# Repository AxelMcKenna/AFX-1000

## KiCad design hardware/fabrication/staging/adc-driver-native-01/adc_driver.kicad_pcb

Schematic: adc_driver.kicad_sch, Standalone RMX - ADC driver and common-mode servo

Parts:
C1, C2, C15, C16: 1pF C0G +/-0.1pF; C_0402_1005Metric
C3, C17: 47pF C0G 5%; C_0805_2012Metric
C4, C5, C18, C19: 22pF C0G 5%; C_0805_2012Metric
C6, C20: 100nF 25V X7R; C_0805_2012Metric
C7, C21: 1uF 63V film 10%; C_Rect_L7.2mm_W5.0mm_P5.00mm
C8, C22: 10uF 16V X7R; C_1206_3216Metric
C9, C23: 47uF 25V X7S; C_1210_3225Metric
C10, C11, C24, C25: 47uF 6.3V X7S; C_1206_3216Metric
C12, C26: 2.2uF 16V X7R; C_0805_2012Metric
C13, C14, C27, C28: 100nF 16V X7R; C_0402_1005Metric
C29, C30, C31, C32: 100nF 50V X7R; C_0805_2012Metric
C33, C34: 10uF 50V X7R; C_1206_3216Metric
C35, C36: 100nF 16V X7R; C_0603_1608Metric
D1, D2: BAT54S,215; SOT-23
J1: Conn_01x03; PinHeader_1x03_P2.54mm_Vertical
J2: Conn_02x10_Odd_Even; PinHeader_2x10_P2.54mm_Vertical
J3, J4: Conn_01x04; PinHeader_1x04_P2.54mm_Vertical
R1, R2, R17, R18: 2.49k 0.05%; R_0402_1005Metric
R3, R4, R19, R20: 1.21k 0.05%; R_0402_1005Metric
R5, R6, R21, R22: 3.3R 1%; R_0805_2012Metric
R7, R23: 1M 1%; R_0805_2012Metric
R8, R9, R24, R25: 100k 0.01%; R_0805_2012Metric
R10, R11, R26, R27: 10k 0.1%; R_0805_2012Metric
R12, R28: 10M 1%; R_0805_2012Metric
R13, R29: 10k 1%; R_0805_2012Metric
R14, R30: 47k 1%; R_0805_2012Metric
R15, R31: 68k 1%; R_0805_2012Metric
R16, R32: 0.1R 1%; R_0805_2012Metric
R33: 1k 1%; R_0805_2012Metric
R34, R36: 100k 0.01%; R_0603_1608Metric
R35, R37, R39, R41: 10k 0.01%; R_0603_1608Metric
R38: 161k 0.01%; R_0805_2012Metric
R40: 240k 0.01%; R_0805_2012Metric
R42, R43: 10k 1%; R_0603_1608Metric
R44: 100k 1%; R_0603_1608Metric
U1, U2: THS4551IDGKR; VSSOP-8_3x3mm_P0.65mm
U3: OPA1656ID; SOIC-8_3.9x4.9mm_P1.27mm
U4: OPA4192ID; SOIC-14_3.9x8.7mm_P1.27mm
U5, U6: LM7705MM/NOPB; VSSOP-8_3x3mm_P0.65mm
U7: TLV9024DR; SOIC-14_3.9x8.7mm_P1.27mm
U8: TPS3808G50DBVR; SOT-23-6

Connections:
/ADC_LN: C3.2, C5.1, J2.4, R6.2
/ADC_LP: C3.1, C4.1, J2.1, R5.2
/ADC_RN: C17.2, C19.1, J2.12, R22.2
/ADC_RP: C17.1, C18.1, J2.9, R21.2
/AGND: C4.2, C5.2, C6.2, C9.2, C10.2, C11.2, C12.2, C13.2, C14.2, C18.2, C19.2, C20.2, C23.2, C24.2, C25.2, C26.2, C27.2, C28.2, C29.2, C30.2, C31.2, C32.2, C33.2, C34.2, C35.2, C36.2, D1.1 (A1), D2.1 (A1), J1.2, J2.3, J2.6, J2.8, J2.11, J2.14, J2.16, J2.20, J3.2, J4.1, R2.1, R7.2, R9.2, R18.1, R23.2, R25.2, R33.2, R39.2, R41.2, R44.2, U5.2 (VSS_A), U5.3 (SD), U5.5 (VSS_B), U6.2 (VSS_A), U6.3 (SD), U6.5 (VSS_B), U7.12, U8.2
/BIAS_OK: J2.18, R42.2, U7.1, U7.2, U7.13, U7.14, U8.3
/BIAS_SHIFT_L: R34.2, R35.1, U7.4, U7.7
/BIAS_SHIFT_R: R36.2, R37.1, U7.8, U7.11
/BUF_L: R1.1, U3.1 (A_OUT), U3.2 (A-)
/BUF_R: R17.1, U3.6 (B-), U3.7 (B_OUT)
/CM_DRIVE_L: C7.1, R12.1, R13.1, U4.7 (B_OUT)
/CM_DRIVE_R: C21.1, R28.1, R29.1, U4.14 (D_OUT)
/CM_SENSE_L: C7.2, R10.2, R11.2, R12.2, U4.6 (B-)
/CM_SENSE_R: C21.2, R26.2, R27.2, R28.2, U4.13 (D-)
/DRV_ENABLE: J2.19, J4.2, R43.1
/DRV_LN: C1.1, R6.1, U1.5 (OUT-)
/DRV_LP: C2.1, R5.1, U1.4 (OUT+)
/DRV_RN: C15.1, R22.1, U2.5 (OUT-)
/DRV_RP: C16.1, R21.1, U2.4 (OUT+)
/FB_N_L: C2.2, R2.2, R4.2, U1.1 (IN-)
/FB_N_R: C16.2, R18.2, R20.2, U2.1 (IN-)
/FB_P_L: C1.2, R1.2, R3.2, U1.8 (IN+)
/FB_P_R: C15.2, R17.2, R19.2, U2.8 (IN+)
/FLY_N_L: C8.2, U5.8 (CF-)
/FLY_N_R: C22.2, U6.8 (CF-)
/FLY_P_L: C8.1, U5.1 (CF+)
/FLY_P_R: C22.1, U6.1 (CF+)
/N12: C30.1, C32.1, C34.1, J3.3, U3.4 (V-), U4.11 (V-)
/NBIAS_L: C11.1, C14.1, J4.3, R15.2, R16.2, R35.2, U1.6 (VS-)
/NBIAS_R: C25.1, C28.1, J4.4, R31.2, R32.2, R37.2, U2.6 (VS-)
/NPUMP_L: C10.1, R16.1, U5.6 (VOUT)
/NPUMP_R: C24.1, R32.1, U6.6 (VOUT)
/P12: C29.1, C31.1, C33.1, J3.1, U3.8 (V+), U4.4 (V+)
/PD_GATED: J2.17, R14.1, R30.1, R43.2, R44.1, U8.1
/PD_L: R14.2, R15.1, U1.7 (PD)
/PD_R: R30.2, R31.1, U2.7 (PD)
/PRE_OUT_L: J1.1, R7.1, U3.3 (A+)
/PRE_OUT_R: J1.3, R23.1, U3.5 (B+)
/REF_ADC1: J2.7, R8.1
/REF_ADC2: J2.15, R24.1
/REF_DIV_L: C6.1, R8.2, R9.1, U4.3 (A+)
/REF_DIV_R: C20.1, R24.2, R25.1, U4.10 (C+)
/REF_HALF_L: U4.1 (A_OUT), U4.2 (A-), U4.5 (B+)
/REF_HALF_R: U4.8 (C_OUT), U4.9 (C-), U4.12 (D+)
/RES_L: C9.1, U5.7 (CRES)
/RES_R: C23.1, U6.7 (CRES)
/SENSE_LN: J2.5, R3.1, R11.1
/SENSE_LP: J2.2, R4.1, R10.1
/SENSE_RN: J2.13, R19.1, R27.1
/SENSE_RP: J2.10, R20.1, R26.1
/THRESH_LOWER: R40.2, R41.1, U7.6, U7.10
/THRESH_UPPER: R38.2, R39.1, U7.5, U7.9
/V5_REG: C12.1, C13.1, C26.1, C27.1, C35.1, C36.1, D1.2 (K2), D2.2 (K2), J3.4, R33.1, R34.1, R36.1, R38.1, R40.1, R42.1, U1.3 (VS+), U2.3 (VS+), U5.4 (VDD), U6.4 (VDD), U7.3, U8.5, U8.6
/VOCM_L: D1.3 (K1_A2), R13.2, U1.2 (VOCM)
/VOCM_R: D2.3 (K1_A2), R29.2, U2.2 (VOCM)

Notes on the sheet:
E12-R2 design-repair candidate; no fabrication or physical qualification
Separate force/sense interface; final ESS pin integration and parasitic model required
Both bias windows and V5 supervisor inhibit PD. DRV_ENABLE requires system rail/reference health.

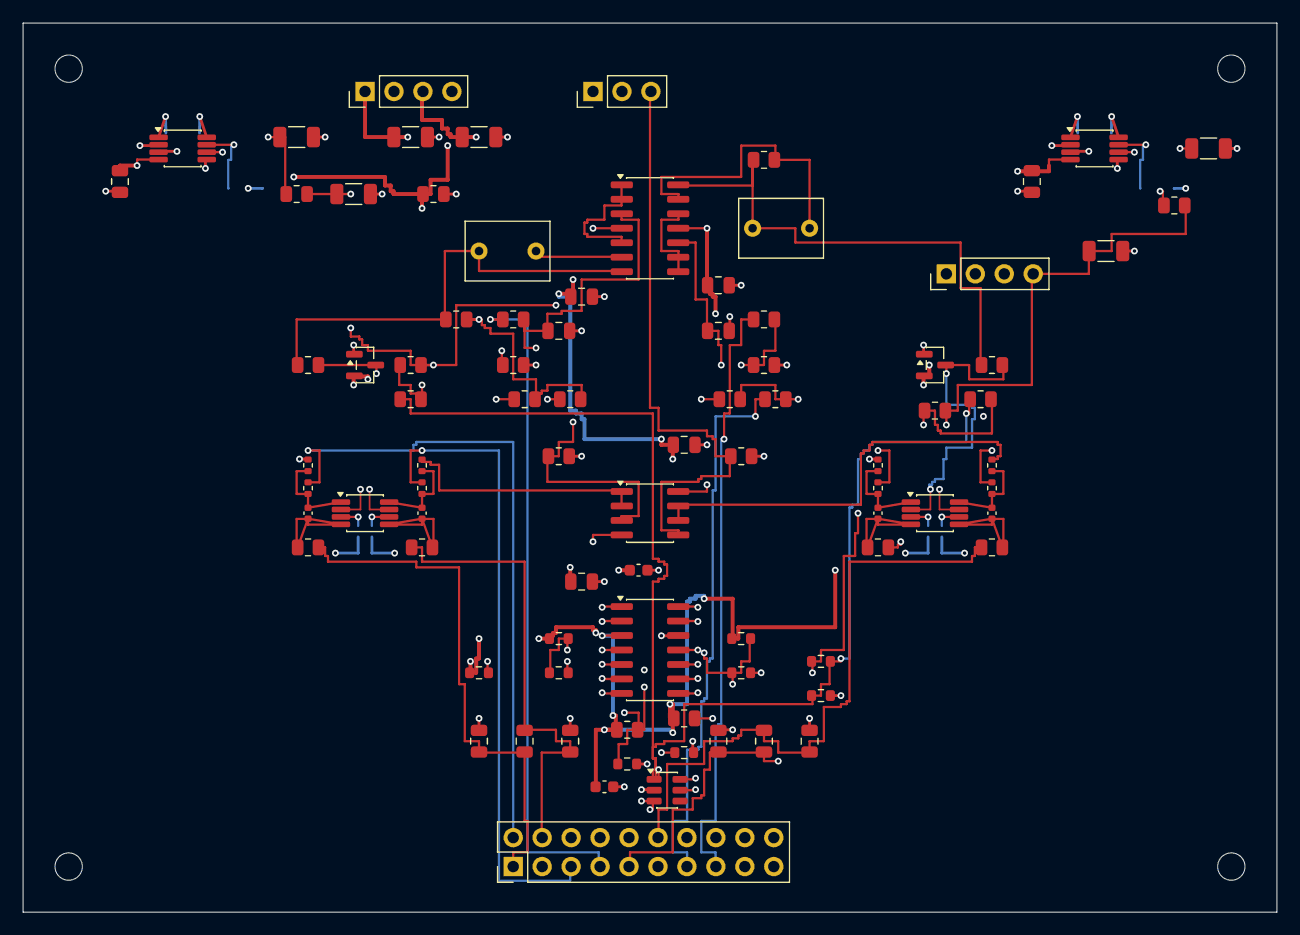
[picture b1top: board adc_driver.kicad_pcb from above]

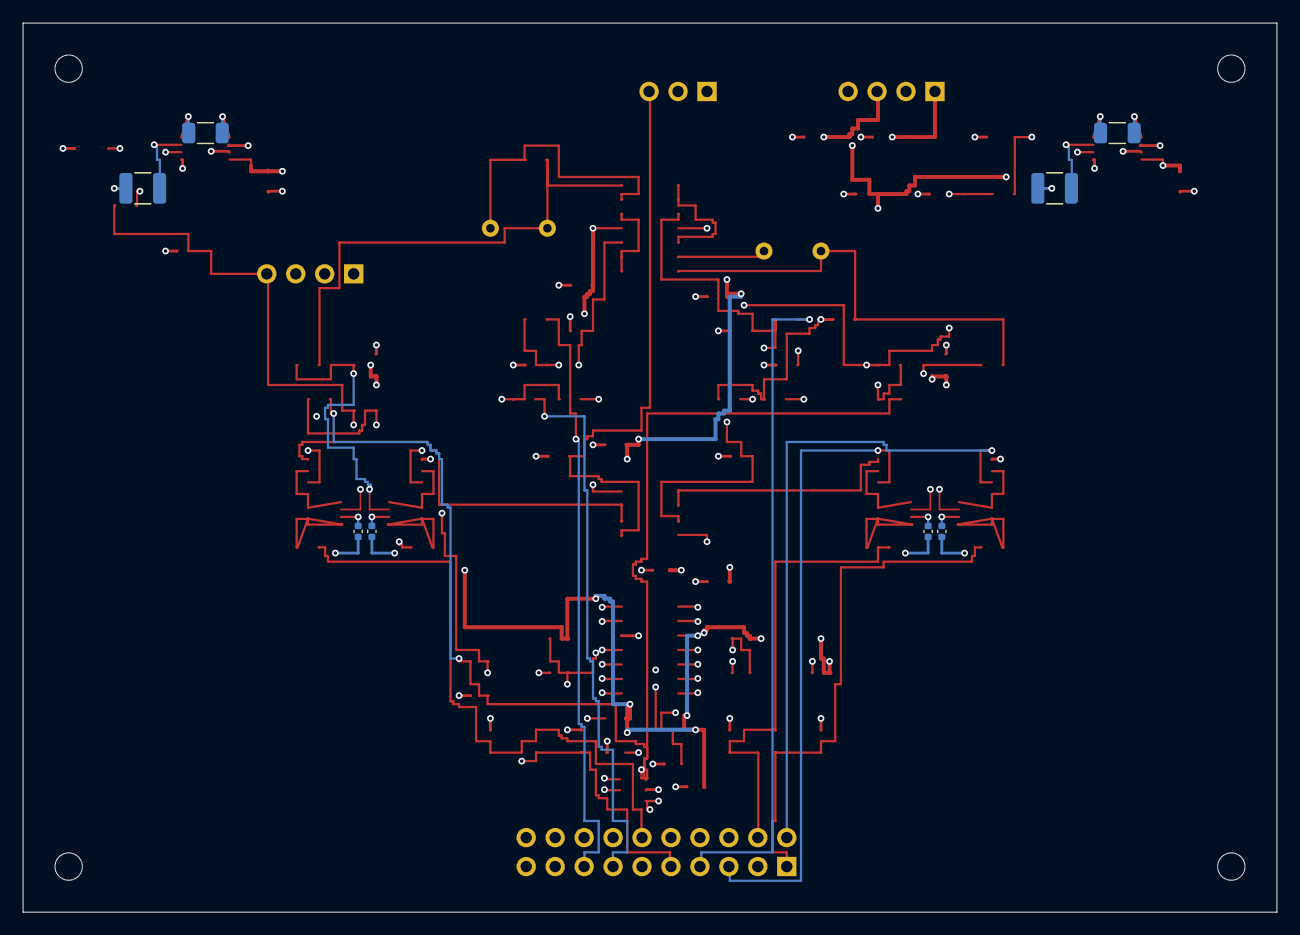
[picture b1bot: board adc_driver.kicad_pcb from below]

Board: 6 copper layers, 110.0 x 78.0 mm, 98 parts (8 on the bottom side), 55 nets.

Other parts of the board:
H1, H2, H3, H4: M2_CLEARANCE; M2_Clearance

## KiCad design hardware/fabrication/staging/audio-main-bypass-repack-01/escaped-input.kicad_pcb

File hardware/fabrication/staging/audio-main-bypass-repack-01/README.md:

# AC04 — bypass-supervisor inputs and unused-space survey

**Input capture and preliminary study only. No revised PCB has been emitted.**
The selected board remains the
[208-open ANALOG_OK revision](../audio-main-controls-06/README.md).

The immutable native capture contains 3,737 native objects and 44 native
control islands from that board. It freezes actual pads, tracks, vias,
authored exclusions and stored reference fill for subsequent planning.

The [space survey](supervisor-space-survey.json) tests moving U605 and C606
together into unused space on the existing 150 × 63 mm board. Proposed
supervisor centres at **(100, 4), (105, 4), (110, 4) and (112, 5) mm** pass
the preliminary receiving, foreign-copper and relocated-ground-via screens.
The (95, 4) mm option is rejected because moved support copper conflicts
with retained copper. The proposed drill-edge-to-SMD gap is approximately
0.170 mm on both faces. These positions do not require a larger housing.

The screen includes the rigidly moved private ground/supply couplers and
every actual SMD land. The relocated ground via is checked as a new hole;
the unchanged-centre exemption is not used. Its intentional moved AGND
spurs are excluded from that obstacle test because they connect at the
hole; all other-net copper and solder lands remain screened. Native DRC
must still check the eventual complete candidate.

The survey assumes four declared old source-entry objects would be
replaced. **Replacement power/sense connections, control routes, native
refill/DRC/ERC/connectivity, full receiving and installed qualification are
unfinished.** No surveyed position is an approved or selected relocation.
The study does not establish heights, mating, harness paths, noise/timing,
fault behaviour or manufacturing acceptance. No supplier message, upload
or order was made, and native Mac CAD remains disabled.

The subsequent distant-supervisor routing draft in this directory is an
unselected experiment. It cannot close all five repaired/new controls within
its original construction targets. Its input captures, applied sources and
partial proposals are retained because the nearer-root comparison explicitly
rechecks three of its routes against new native geometry. No final native-clean
board is claimed here. See the [cleaned near-root comparison](../audio-main-bypass-repack-04/README.md).

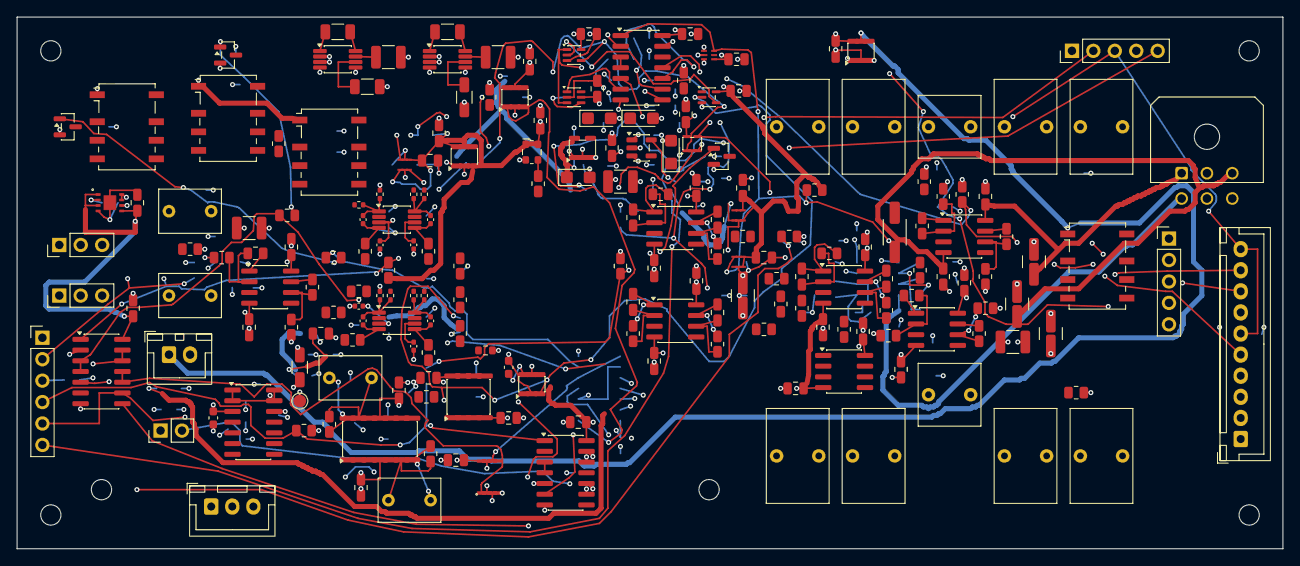
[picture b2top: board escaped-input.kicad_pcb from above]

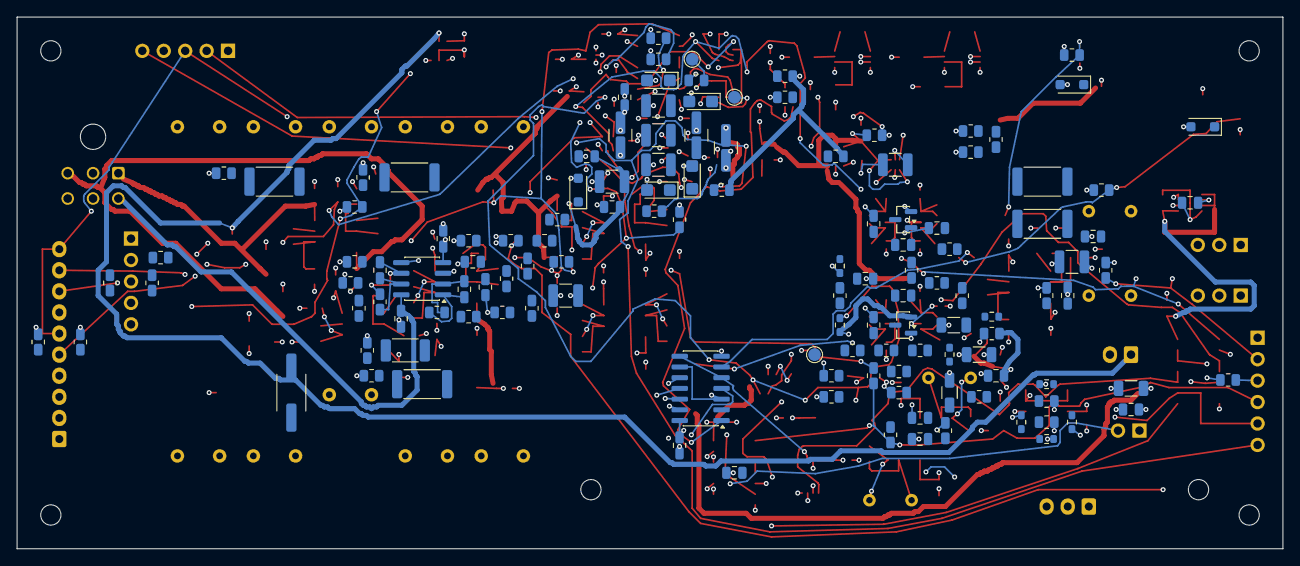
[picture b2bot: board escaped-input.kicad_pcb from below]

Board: 4 copper layers, 150.0 x 63.0 mm, 334 parts (129 on the bottom side), 176 nets.

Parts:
C101, C102, C115, C116: 1pF C0G +/-0.1pF; C_0402_1005Metric
C103, C117: 47pF C0G 5%; C_0805_2012Metric
C104, C105, C118, C119: 22pF C0G 5%; C_0805_2012Metric
C106, C120: 100nF 25V X7R; C_0805_2012Metric
C107, C121: 1uF 63V film 10%; C_Rect_L7.2mm_W5.0mm_P5.00mm
C108, C122: 10uF 16V X7R; C_1206_3216Metric
C109, C123: 47uF 25V X7S; C_1210_3225Metric
C110, C111, C124, C125: 47uF 6.3V X7S; C_1206_3216Metric
C112, C126: 2.2uF 16V X7R; C_0805_2012Metric
C113, C114, C127, C128: 100nF 16V X7R; C_0402_1005Metric
C129, C130, C131, C132, C220, C221, C222, C223, C224, C225, C226, C228, C229, C311, C312, C313, C314, C315, C316, C317, C318, C323, C324, C405, C406, C505, C506, C507, C508: 100nF 50V X7R; C_0805_2012Metric
C133, C134: 10uF 50V X7R; C_1206_3216Metric
C135, C136: 100nF 16V X7R; C_0603_1608Metric
C201, C202, C205: 1uF 10V X7R 10%; C_0805_2012Metric
C203, C210, C212, C214: 100nF 50V C0G 5%; C_1210_3225Metric
C204, C206, C207, C208, C209, C211, C213, C215: 1uF 10V tantalum 10%; CP_EIA-3216-18_Kemet-A
C216, C218, C227: 2.2uF 25V X7R 10%; C_1210_3225Metric
C217, C219: 10uF 16V X7R 10%; C_1210_3225Metric
C230, C231, C232, C610, C611, C612: 100nF 16V X7R; C_0805_2012Metric
C301, C302, C306, C307: 510pF 50V C0G 2%; C_0805_2012Metric
C303, C308: 51pF 50V C0G 2%; C_0805_2012Metric
C304, C305, C309, C310: 1nF 50V C0G 1%; C_0805_2012Metric
C319, C320, C509, C510, C511, C512: 10uF 50V X7R; C_1210_3225Metric
C321, C322: 2.2uF film 63V 10%; C_Rect_L7.2mm_W7.2mm_P5.00mm_FKS2_FKP2_MKS2_MKP2
C401, C403: 1uF film 63V 10%; C_Rect_L7.2mm_W5.0mm_P5.00mm
C402, C404: 47pF 50V C0G 5%; C_0805_2012Metric
C407, C408: 10uF 50V X7R 10%; C_1210_3225Metric
C501, C502, C503, C504, C513, C514, C515, C516: 4.7uF film 63V 10%; C_Rect_L7.2mm_W11.0mm_P5.00mm_FKS2_FKP2_MKS2_MKP2
C601: 150pF C0G 5%; C_0805_2012Metric
C602, C603, C604, C605, C606: 100nF X7R; C_0805_2012Metric
C607: 1uF 16V X7R; C_0805_2012Metric
C608: 22uF 16V X7R; C_1206_3216Metric
C609: 1uF 16V X7R 10%; C_0805_2012Metric
D101, D102: BAT54S,215; SOT-23
D601, D602, D603: SMF9.0A; D_SOD-123F
H1, H2, H3, H4: M2_CLEARANCE; M2_Clearance
H5, H6: M2_SHARED_SUPPORT; M2_Clearance
J203, J603: Conn_01x05; PinHeader_1x05_P2.54mm_Vertical
J402: B10B-XH-A(LF)(SN); JST_XH_B10B-XH-A_1x10_P2.50mm_Vertical
J403: B3B-XH-A(LF)(SN); JST_XH_B3B-XH-A_1x03_P2.50mm_Vertical
J602: Conn_01x06; PinHeader_1x06_P2.54mm_Vertical
J606: Conn_01x02; PinHeader_1x02_P2.54mm_Vertical
J607, J608: Conn_01x03; PinHeader_1x03_P2.54mm_Vertical
J701: 43045-0600; Molex_Micro-Fit_3.0_43045-0600_2x03_P3.00mm_Horizontal
J702: B2B-XH-A(LF)(SN); JST_XH_B2B-XH-A_1x02_P2.50mm_Vertical
K401, K503, K601, K602: G6K-2F-Y DC5; Relay_DPDT_Omron_G6K-2F-Y
Q601, Q602, Q603: AO3400A; SOT-23
R101, R102, R117, R118: 2.49k 0.05%; R_0402_1005Metric
R103, R104, R119, R120: 1.21k 0.05%; R_0402_1005Metric
R105, R106, R121, R122: 3.3R 1%; R_0805_2012Metric
R107, R123: 1M 1%; R_0805_2012Metric
R108, R109, R124, R125: 100k 0.01%; R_0805_2012Metric
R110, R111, R126, R127, R212: 10k 0.1%; R_0805_2012Metric
R112, R128: 10M 1%; R_0805_2012Metric
R113, R129, R203, R204, R601, R606: 10k 1%; R_0805_2012Metric
R114, R130, R205, R206, R603, R604, R605, R607, R615: 47k 1%; R_0805_2012Metric
R115, R131: 68k 1%; R_0805_2012Metric
R116, R132: 0.1R 1%; R_0805_2012Metric
R133: 1k 1%; R_0805_2012Metric
R134, R136: 100k 0.01%; R_0603_1608Metric
R135, R137, R139, R141: 10k 0.01%; R_0603_1608Metric
R138: 161k 0.01%; R_0805_2012Metric
R140: 240k 0.01%; R_0805_2012Metric
R142, R143: 10k 1%; R_0603_1608Metric
R144: 100k 1%; R_0603_1608Metric
R201, R202: 2k 1%; R_0805_2012Metric
R207, R208, R209, R210, R517, R518, R602, R617, R618: 100k 1%; R_0805_2012Metric
R211: 27.7k 0.1%; R_0805_2012Metric
R213, R214, R215, R216: 33 1%; R_0805_2012Metric
R301, R302, R313, R314: 1.8k 0.1%; R_0805_2012Metric
R303, R304, R315, R316: 4.3 1%; R_0805_2012Metric
R305, R306, R317, R318: 100k 0.1%; R_0805_2012Metric
R307, R319: 1.2M 0.1%; R_0805_2012Metric
R308, R309, R310, R311, R320, R321, R322, R323: 499 0.01%; R_0805_2012Metric
R312, R324, R407, R414: 33.2 0.1%; R_0805_2012Metric
R325, R326, R401, R408: 33.2k 0.1%; R_0805_2012Metric
R327, R328: 2.74k 0.1% 0.5W; R_2010_5025Metric
R402, R409: 13.7k 0.1%; R_0805_2012Metric
R403, R410: 4.99k 0.1% 1W; R_2512_6332Metric
R404, R411: 68k 0.1%; R_0805_2012Metric
R405, R412: 365 0.1%; R_0805_2012Metric
R406, R413, R502, R506: 1k 0.1%; R_0805_2012Metric
R501, R505: 5.23k 0.1%; R_0805_2012Metric
R503, R507, R511, R515: 100 1% 1W; R_2512_6332Metric
R504, R508, R512, R516: 20k 1%; R_0805_2012Metric
R509, R513: 1.21k 0.1%; R_0805_2012Metric
R510, R514: 2k 0.1%; R_0805_2012Metric
R608, R610, R612: 4.7k 1%; R_0805_2012Metric
R609, R611, R613: 270k 1%; R_0805_2012Metric
R614: 383k 0.1% 25ppm; R_0805_2012Metric
R616: 147k 1%; R_0805_2012Metric
TP401: TEST_ONLY_ADC_DRV_ENABLE; TestPoint_Pad_D1.5mm
TP402: TEST_ONLY_CHIP_EN; TestPoint_Pad_D1.5mm
TP403: TEST_ONLY_PD_GATED; TestPoint_Pad_D1.5mm
TP404: TEST_ONLY_AGND; TestPoint_Pad_D1.5mm
U101, U102: THS4551IDGKR; VSSOP-8_3x3mm_P0.65mm
U103, U305, U401: OPA1656ID; SOIC-8_3.9x4.9mm_P1.27mm
U104: OPA4192ID; SOIC-14_3.9x8.7mm_P1.27mm
U105, U106: LM7705MM/NOPB; VSSOP-8_3x3mm_P0.65mm
U107: TLV9024DR; SOIC-14_3.9x8.7mm_P1.27mm
U108, U605: TPS3808G50DBVR; SOT-23-6
U202: TPS7A2033PDBVR; SOT-23-5
U203: TPS7A2045PDBVR; SOT-23-5
U204, U205, U208: TPS389033DSET; TI_DSE0006A_TPS3890
U206: TPS389001DSET; TI_DSE0006A_TPS3890
U207, U602, U606: SN74HCS08DR; SOIC-14_3.9x8.7mm_P1.27mm
U209, U212: SN74LVC1G08DCKR; SOT-353_SC-70-5
U210: SN74LVC2G17DCKR; SOT-363_SC-70-6
U211: SN74LVC1G17DCKR; SOT-353_SC-70-5
U301, U302, U303, U304, U502: OPA1612AID; SOIC-8_3.9x4.9mm_P1.27mm
U501: OPA2992D; SOIC-8_3.9x4.9mm_P1.27mm
U601: TPS3431SDRBR; TI_DRB0008A_TPS3431
U603: SN74LVC1G74DCTR; TI_DCT0008A_SN74LVC1G74
U604: TPS3808G33DBVR; SOT-23-6
U607: LTC6994HS6-1#TRMPBF; TSOT-23-6
U608: SN74HCS86DR; SOIC-14_3.9x8.7mm_P1.27mm
Y201: ECS-2520MVLC-245.7-BN-TR; Oscillator_SMD_ECS_2520MV-xxx-xx-4Pin_2.5x2.0mm

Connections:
5V_DIG: C608.1, J702.1, K401.1, K503.1, K601.1, K602.1, U605.5
/ADC/BIAS_SHIFT_L: R134.2, R135.1, U107.4, U107.7
/ADC/BIAS_SHIFT_R: R136.2, R137.1, U107.8, U107.11
/ADC/BUF_L: R101.1, U103.1, U103.2
/ADC/BUF_R: R117.1, U103.6, U103.7
/ADC/CM_DRIVE_L: C107.1, R112.1, R113.1, U104.7
/ADC/CM_DRIVE_R: C121.1, R128.1, R129.1, U104.14
/ADC/CM_SENSE_L: C107.2, R110.2, R111.2, R112.2, U104.6
/ADC/CM_SENSE_R: C121.2, R126.2, R127.2, R128.2, U104.13
/ADC/DRV_LN: C101.1, R106.1, U101.5
/ADC/DRV_LP: C102.1, R105.1, U101.4
/ADC/DRV_RN: C115.1, R122.1, U102.5
/ADC/DRV_RP: C116.1, R121.1, U102.4
/ADC/FB_N_L: C102.2, R102.2, R104.2, U101.1
/ADC/FB_N_R: C116.2, R118.2, R120.2, U102.1
/ADC/FB_P_L: C101.2, R101.2, R103.2, U101.8
/ADC/FB_P_R: C115.2, R117.2, R119.2, U102.8
/ADC/FLY_N_L: C108.2, U105.8
/ADC/FLY_N_R: C122.2, U106.8
/ADC/FLY_P_L: C108.1, U105.1
/ADC/FLY_P_R: C122.1, U106.1
/ADC/NBIAS_L: C111.1, C114.1, J403.2, R115.2, R116.2, R135.2, U101.6
/ADC/NBIAS_R: C125.1, C128.1, J403.3, R131.2, R132.2, R137.2, U102.6
/ADC/NPUMP_L: C110.1, R116.1, U105.6
/ADC/NPUMP_R: C124.1, R132.1, U106.6
/ADC/PD_GATED: R114.1, R130.1, R143.2, R144.1, TP403.1, U108.1
/ADC/PD_L: R114.2, R115.1, U101.7
/ADC/PD_R: R130.2, R131.1, U102.7
/ADC/REF_DIV_L: C106.1, R108.2, R109.1, U104.3
/ADC/REF_DIV_R: C120.1, R124.2, R125.1, U104.10
/ADC/REF_HALF_L: U104.1, U104.2, U104.5
/ADC/REF_HALF_R: U104.8, U104.9, U104.12
/ADC/RES_L: C109.1, U105.7
/ADC/RES_R: C123.1, U106.7
/ADC/THRESH_LOWER: R140.2, R141.1, U107.6, U107.10
/ADC/THRESH_UPPER: R138.2, R139.1, U107.5, U107.9
/ADC/VOCM_L: D101.3, R113.2, U101.2
/ADC/VOCM_R: D102.3, R129.2, U102.2
/BYPASS/ARMED: J602.5, U602.9, U603.3
/BYPASS/BYPASS_GATE: Q601.1, R608.2, R609.1
/BYPASS/BYPASS_LOW: D601.1, K601.8, Q601.3
/BYPASS/BYPASS_SENSE: J602.6, J603.5, R606.2
/BYPASS/CLEAR_N: U603.6, U606.5, U606.8
/BYPASS/COIL_ENABLE: U602.8, U606.4
/BYPASS/CWD: C601.1, U601.2
/BYPASS/FINAL_ENABLE: R608.1, U606.6
/BYPASS/GAIN_DELAY: C609.1, R615.2, U608.2
/BYPASS/GAIN_EDGE: U608.3, U608.4
/BYPASS/GAIN_GATE: Q602.1, R610.2, R611.1
/BYPASS/GAIN_REQ: J602.4, R607.1, R610.1, R615.1, U608.1
/BYPASS/GAIN_STABLE: U606.13, U608.6
/BYPASS/HEARTBEAT: J602.2, R602.1, U601.6
/BYPASS/INPUT_ENABLE: R612.1, U602.3, U602.4, U606.12
/BYPASS/INPUT_GATE: Q603.1, R612.2, R613.1
/BYPASS/INPUT_LOW: D603.1, K602.8, Q603.3
/BYPASS/INPUT_READY: J606.2, U606.3, U606.9
/BYPASS/IN_L: J607.1, K601.2, K602.4
/BYPASS/IN_R: J607.3, K601.7, K602.5
/BYPASS/LOCAL_OK: R601.2, U601.7, U601.8, U602.1, U604.1, U605.1
/BYPASS/MCU_PERMIT: J602.3, R603.1, U602.12, U602.13
/BYPASS/OUT_L: J608.1, K601.3
/BYPASS/OUT_R: J608.3, K601.6
/BYPASS/PERMIT_CLEAN: U602.10, U602.11, U603.1
/BYPASS/PROCESS_HEALTH: U602.6, U606.10
/BYPASS/PROCESS_OK: J603.2, R604.1, U602.5
/BYPASS/STARTUP_CT: R618.2, U604.4
/BYPASS/TIMER_DIV: R616.2, R617.1, U607.4
/BYPASS/TIMER_ENABLE: U606.1, U606.11, U607.1
/BYPASS/TIMER_INPUT_OK: U606.2, U607.6
/BYPASS/TIMER_SET: R614.1, U607.3
/CODEC/A3V3: C205.1, C217.1, C229.1, U202.5, U205.1
/CODEC/A4V5: C207.1, C219.1, R211.1, U203.5
/CODEC/ADC_BIAS_IO: U211.4, U212.2
/CODEC/ADC_DATA: J203.4, R216.2
/CODEC/BCLK: J203.2, R214.2
/CODEC/CHIP_REQUEST: U207.6, U210.1
/CODEC/CLK_VALID: R207.1, U207.9
/CODEC/CODEC_FLAGS: U207.8, U207.13
/CODEC/CODEC_PGOOD: J402.9, R203.1, U204.6, U205.6, U206.6, U207.1
/CODEC/CODEC_RUN: J402.5, R205.1, U207.5
/CODEC/CT_SETTLE: C227.1, U208.5
/CODEC/DRIVER_SETTLE_READY: U208.3, U209.1, U212.4
/CODEC/MCLK_SRC: R213.1, Y201.3
/CODEC/PRE_ANALOG_OK: J402.8, R206.1, U207.2
/CODEC/RAMP_DONE: R208.1, U207.10
/CODEC/REF_DAC_BUF: C203.1, C204.1
/CODEC/REF_PLL: C210.1, C211.1
/CODEC/SCL: J402.3, R201.1
/CODEC/SDA: J402.4, R202.1
/CODEC/SENSE_4V5: R211.2, R212.1, U206.1
/CODEC/SETTLE_ENABLE: U207.11, U210.3, U212.1
/CODEC/SUPPLY_OK: U207.3, U207.4
/CODEC/TIMER_OK: R204.1, U208.6, U209.2
/CODEC/WS: J203.3, R215.2
/DAC/BIAS_N_L: R304.2, U301.5
/DAC/BIAS_N_R: R316.2, U302.5
/DAC/BIAS_P_L: R303.2, U301.3
/DAC/BIAS_P_R: R315.2, U302.3
/DAC/BUF_IN_L: R327.2, U305.3
/DAC/BUF_IN_R: R328.2, U305.5
/DAC/BUF_OUT_L: R312.1, U305.1, U305.2
/DAC/BUF_OUT_R: R324.1, U305.6, U305.7
/DAC/CM_DRV_L: C303.2, R303.1, R304.1, R307.2, U303.1
/DAC/CM_DRV_R: C308.2, R315.1, R316.1, R319.2, U303.7
/DAC/CM_SUM_L: C303.1, R305.2, R306.2, R307.1, U303.2
/DAC/CM_SUM_R: C308.1, R317.2, R318.2, R319.1, U303.6
/DAC/HP_NODE_L: C321.2, R325.1, R327.1
/DAC/HP_NODE_R: C322.2, R326.1, R328.1
/DAC/IV_N_L: C302.2, R302.2, R306.1, R309.1, U301.7
/DAC/IV_N_R: C307.2, R314.2, R318.1, R321.1, U302.7
/DAC/IV_P_L: C301.2, R301.2, R305.1, R308.1, U301.1
/DAC/IV_P_R: C306.2, R313.2, R317.1, R320.1, U302.1
/DAC/RX_NEG_L: C304.1, R308.2, R310.1, U304.2
/DAC/RX_NEG_R: C309.1, R320.2, R322.1, U304.6
/DAC/RX_OUT_L: C304.2, C321.1, R310.2, U304.1
/DAC/RX_OUT_R: C309.2, C322.1, R322.2, U304.7
/DAC/RX_POS_L: C305.1, R309.2, R311.1, U304.3
/DAC/RX_POS_R: C310.1, R321.2, R323.1, U304.5
/INPUT/ATTN_L: K401.2, R401.2, R402.1
/INPUT/ATTN_R: K401.7, R408.2, R409.1
/INPUT/BUF_IN_L: C401.2, C402.1, R404.1, U401.3
/INPUT/BUF_IN_R: C403.2, C404.1, R411.1, U401.5
/INPUT/BUF_OUT_L: R405.2, R407.1, U401.1
/INPUT/BUF_OUT_R: R412.2, R414.1, U401.7
/INPUT/GAIN_FB_L: R405.1, R406.1, U401.2
/INPUT/GAIN_FB_R: R412.1, R413.1, U401.6
/INPUT/HP_SRC_L: C401.1, R403.2
/INPUT/HP_SRC_R: C403.1, R410.2
/INPUT/RANGE_L: K401.3, R403.1
/INPUT/RANGE_R: K401.6, R410.1
/OUTPUT/M_AC_L: C501.2, C513.2, K503.2, R504.1
/OUTPUT/M_AC_R: C502.2, C514.2, K503.7, R508.1
/OUTPUT/M_DRV_L: R501.2, R503.1, U501.1
/OUTPUT/M_DRV_R: R505.2, R507.1, U501.7
/OUTPUT/M_FB_L: R501.1, R502.1, U501.2
/OUTPUT/M_FB_R: R505.1, R506.1, U501.6
/OUTPUT/M_SER_L: C501.1, C513.1, R503.2
/OUTPUT/M_SER_R: C502.1, C514.1, R507.2
/OUTPUT/S_AC_L: C503.2, C515.2, K503.4, R512.1
/OUTPUT/S_AC_R: C504.2, C516.2, K503.5, R516.1
/OUTPUT/S_DRV_L: R509.2, R511.1, U502.1
/OUTPUT/S_DRV_R: R513.2, R515.1, U502.7
/OUTPUT/S_FB_L: R509.1, R510.1, U502.2
/OUTPUT/S_FB_R: R513.1, R514.1, U502.6
/OUTPUT/S_SER_L: C503.1, C515.1, R511.2
/OUTPUT/S_SER_R: C504.1, C516.1, R515.2
ADC_BIAS_WINDOW_OK: R142.2, U107.1, U107.2, U107.13, U107.14, U108.3, U211.2
ADC_DRV_ENABLE: R143.1, TP401.1, U210.4
ADC_LN: C103.2, C105.1, R103.1, R106.2, R111.1
ADC_LP: C103.1, C104.1, R104.1, R105.2, R110.1
ADC_RN: C117.2, C119.1, R119.1, R122.2, R127.1
ADC_RP: C117.1, C118.1, R120.1, R121.2, R126.1
AGND: C104.2, C105.2, C106.2, C109.2, C110.2, C111.2, C112.2, C113.2, C114.2, C118.2, C119.2, C120.2, C123.2, C124.2, C125.2, C126.2, C127.2, C128.2, C129.2, C130.2, C131.2, C132.2, C133.2, C134.2, C135.2, C136.2, C201.2, C202.2, C203.2, C204.2, C205.2, C206.2, C207.2, C208.2, C209.2, C210.2, C211.2, C212.2, C213.2, C214.2, C215.2, C216.2, C217.2, C218.2, C219.2, C220.2, C221.2, C222.2, C223.2, C224.2, C225.2, C226.2, C227.2, C228.2, C229.2, C230.2, C231.2, C232.2, C305.2, C310.2, C311.2, C312.2, C313.2, C314.2, C315.2, C316.2, C317.2, C318.2, C319.2, C320.2, C323.2, C324.2, C402.2, C404.2, C405.2, C406.2, C407.2, C408.2, C505.2, C506.2, C507.2, C508.2, C509.2, C510.2, C511.2, C512.2, C601.2, C602.2, C603.2, C604.2, C605.2, C606.2, C607.2, C608.2, C609.2, C610.2, C611.2, C612.2, D101.1, D102.1, D601.2, D602.2, D603.2, J203.1, J402.1, J402.7, J403.1, J602.1, J603.4, J606.1, J607.2, J608.2, J701.2, J702.2, Q601.2, Q602.2, Q603.2, R102.1, R107.2, R109.2, R118.1, R123.2, R125.2, R133.2, R139.2, R141.2, R144.2, R205.2, R206.2, R207.2, R208.2, R209.2, R210.2, R212.2, R311.2, R323.2, R325.2, R326.2, R402.2, R404.2, R406.2, R409.2, R411.2, R413.2, R502.2, R504.2, R506.2, R508.2, R510.2, R512.2, R514.2, R516.2, R517.2, R518.2, R602.2, R603.2, R604.2, R605.2, R607.2, R609.2, R611.2, R613.2, R614.2, R617.2, TP404.1, U105.2, U105.3, U105.5, U106.2, U106.3, U106.5, U107.12, U108.2, U202.2, U203.2, U204.2, U205.2, U206.2, U207.7, U208.2, U209.3, U210.2, U211.3, U212.3, U303.3, U303.5, U601.4, U601.9, U602.7, U603.4, U604.2, U605.2, U606.7, U607.2, U608.7, U608.9, U608.10, U608.12, U608.13, Y201.2
ANALOG_OK: J402.6, J402.10, J603.3, R210.1, R605.1, U209.4, U602.2
CHIP_EN: R209.1, TP402.1, U207.12, U210.6
DAC_LN: C302.1, R302.1, U301.6
DAC_LP: C301.1, R301.1, U301.2
DAC_RN: C307.1, R314.1, U302.6
DAC_RP: C306.1, R313.1, U302.2
GAIN_LOW: D602.1, K401.8, K503.8, Q602.3
N12: C130.1, C132.1, C134.1, C312.1, C314.1, C316.1, C318.1, C320.1, C324.1, C406.1, C408.1, C508.1, C512.1, J701.5, U103.4, U104.11, U301.4, U302.4, U303.4, U304.4, U305.4, U401.4, U502.4
N19: C506.1, C510.1, J701.3, U501.4
P12: C129.1, C131.1, C133.1, C311.1, C313.1, C315.1, C317.1, C319.1, C323.1, C405.1, C407.1, C507.1, C511.1, J701.4, U103.8, U104.4, U301.8, U302.8, U303.8, U304.8, U305.8, U401.8, U502.8
P19: C505.1, C509.1, J701.1, U501.8
PRE_OUT_L: R107.1, R407.2, U103.3
PRE_OUT_R: R123.1, R414.2, U103.5
PROC_IN_L: K401.4, K602.3, R401.1
PROC_IN_R: K401.5, K602.6, R408.1
PROC_OUT_L: K503.3, K601.4
PROC_OUT_R: K503.6, K601.5
RECV_L: R312.2, R517.1, U501.3, U502.3
RECV_R: R324.2, R518.1, U501.5, U502.5
REF_ADC1: C212.1, C213.1, R108.1
REF_ADC2: C214.1, C215.1, R124.1
V3V3_IO: C201.1, C220.1, C221.1, C222.1, C223.1, C224.1, C225.1, C226.1, C228.1, C230.1, C231.1, C232.1, C602.1, C603.1, C604.1, C605.1, C606.1, C607.1, C610.1, C611.1, C612.1, J402.2, J603.1, R201.2, R202.2, R203.2, R204.2, R601.1, R606.1, R616.1, R618.1, U204.1, U204.3, U204.4, U205.3, U205.4, U206.3, U206.4, U207.14, U208.1, U208.4, U209.5, U210.5, U211.5, U212.5, U601.1, U601.3, U601.5, U602.14, U603.2, U603.7, U603.8, U604.3, U604.5, U604.6, U605.3, U605.6, U606.14, U607.5, U608.5, U608.14, Y201.1, Y201.4
V5_REG: C112.1, C113.1, C126.1, C127.1, C135.1, C136.1, C216.1, C218.1, D101.2, D102.2, J701.6, R133.1, R134.1, R136.1, R138.1, R140.1, R142.1, U101.3, U102.3, U105.4, U106.4, U107.3, U108.5, U108.6, U202.1, U202.3, U203.1, U203.3
